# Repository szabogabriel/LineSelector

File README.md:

# LineSelector

This project is a blueprint for a LineSelector guitar effect (something similar to Boss LS2, hence the name).

It doesn't have an input signal attenuation, since it wouldn't fit the case.

The goal would be to be able to select the order of the effects on the fly. Currently the current options are planned:

* Bypass (arguably a true one)
* Pedal A
* Pedal B
* Pedal A -> B
* Pedal B -> A
* Pedals A and B parallel

All of these should be set via the two fotswitches (one for each channel). Planned operations:

* Nothing selected after boot
* Switch A -> Toggle status of input A. If B is active and A is activated, create chain B -> A.
* Switch B -> Toggle status of input B. If A is active and B is activated, create chain A -> B.
* Switch A+B simultaneously -> Toggle A/B in parallel operation. It should activate parallel state, even if one of the pedals is currently active.

The logic will be implemented in an Arduino Micro.

Currently the PCB is designed, not yet tested.

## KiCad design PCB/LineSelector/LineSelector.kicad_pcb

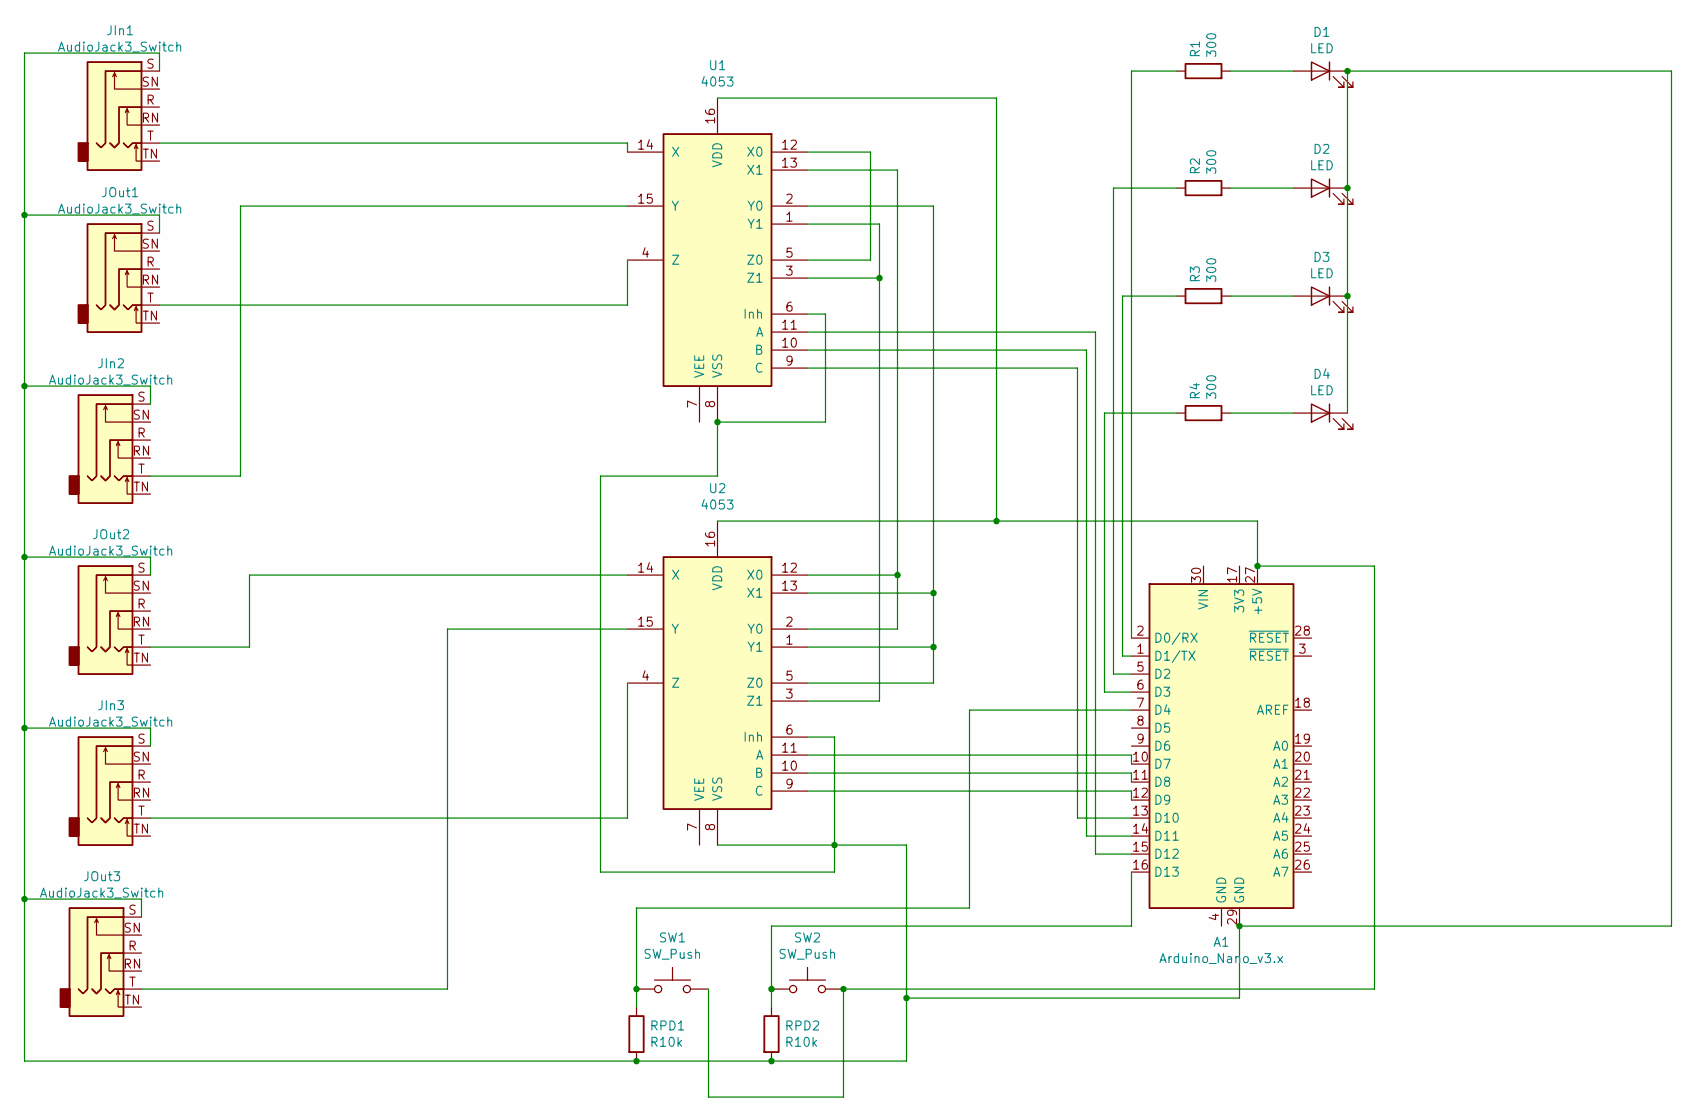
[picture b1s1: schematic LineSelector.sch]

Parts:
A1: Arduino_Nano_v3.x; Arduino_Nano
D1, D2, D3, D4: LED; LED_D5.0mm
JIn1, JIn2, JIn3: AudioJack3_Switch; Jack_3.5mm_Neutrik_NMJ6HCD2_Horizontal
JOut1, JOut2, JOut3: AudioJack3_Switch; Jack_3.5mm_Neutrik_NMJ6HCD2_Horizontal
R1, R2, R3, R4: 300; R_Axial_DIN0411_L9.9mm_D3.6mm_P7.62mm_Vertical
RPD1, RPD2: R10k; R_Axial_DIN0411_L9.9mm_D3.6mm_P7.62mm_Vertical
SW1, SW2: SW_Push; SW_PUSH_6mm_H4.3mm
U1, U2: 4053; DIP-16_W10.16mm

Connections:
unnamed: A1.1 (D1/TX), R3.1
unnamed: A1.2 (D0/RX), R1.1
unnamed: A1.5 (D2), R2.1
unnamed: A1.6 (D3), R4.1
unnamed: A1.7 (D4), RPD1.1, SW1.1
unnamed: A1.10 (D7), U2.11 (A)
unnamed: A1.11 (D8), U2.10 (B)
unnamed: A1.12 (D9), U2.9 (C)
unnamed: A1.13 (D10), U1.9 (C)
unnamed: A1.14 (D11), U1.10 (B)
unnamed: A1.15 (D12), U1.11 (A)
unnamed: A1.16 (D13), RPD2.1, SW2.1
unnamed: A1.27 (+5V), SW1.2, SW2.2, U1.16 (VDD), U2.16 (VDD)
unnamed: A1.29 (GND), D1.1 (K), D2.1 (K), D3.1 (K), D4.1 (K), JIn1.S, JIn2.S, JIn3.S, JOut1.S, JOut2.S, JOut3.S, RPD1.2, RPD2.2, U1.6 (Inh), U1.8 (VSS), U2.6 (Inh), U2.8 (VSS)
unnamed: D1.2 (A), R1.2
unnamed: D2.2 (A), R2.2
unnamed: D3.2 (A), R3.2
unnamed: D4.2 (A), R4.2
unnamed: JIn1.T, U1.14 (X)
unnamed: JIn2.T, U1.15 (Y)
unnamed: JIn3.T, U2.4 (Z)
unnamed: JOut1.T, U1.4 (Z)
unnamed: JOut2.T, U2.14 (X)
unnamed: JOut3.T, U2.15 (Y)
unnamed: U1.1 (Y1), U1.3 (Z1), U2.3 (Z1)
unnamed: U1.2 (Y0), U2.1 (Y1), U2.5 (Z0), U2.13 (X1)
unnamed: U1.5 (Z0), U1.12 (X0)
unnamed: U1.13 (X1), U2.2 (Y0), U2.12 (X0)

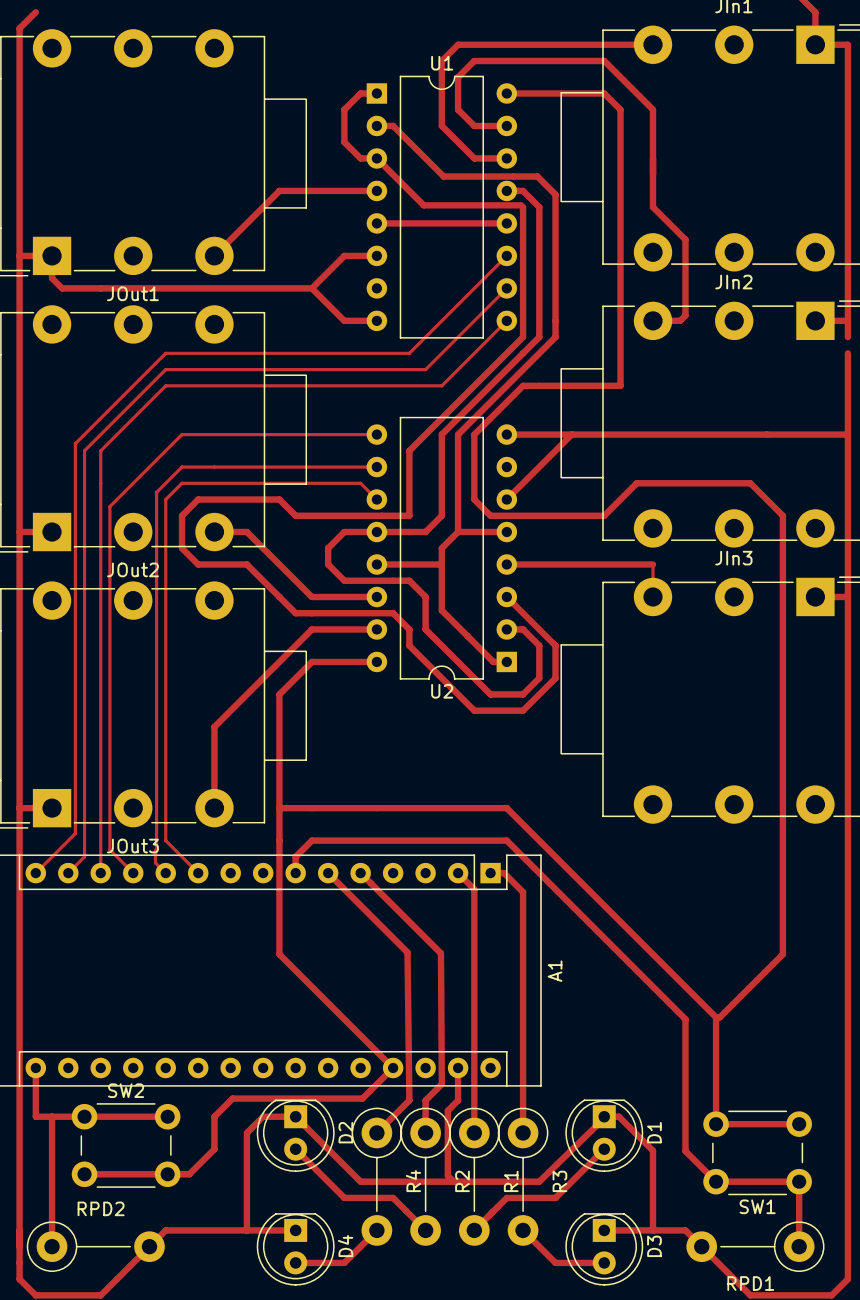
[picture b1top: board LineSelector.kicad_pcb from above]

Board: 2 copper layers, 21 parts (0 on the bottom side), 28 nets.
